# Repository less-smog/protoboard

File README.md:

TODO:

* Align I2C output pins with the rest, so that the pins can be plugged into the edge of a protoboard.
* Move resistors and diodes to reduce offset from the edge - ideally there should be none.
* SDS011 connector should be an angled connector, close to the edge of the board.

## Subtree workflow

### Inject

```
git subtree add --prefix vendor/lolin https://github.com/tommck/LoLin_Designs.git master --squash
```

### Update

```
git subtree pull --prefix vendor/lolin https://github.com/tommck/LoLin_Designs.git master --squash
```

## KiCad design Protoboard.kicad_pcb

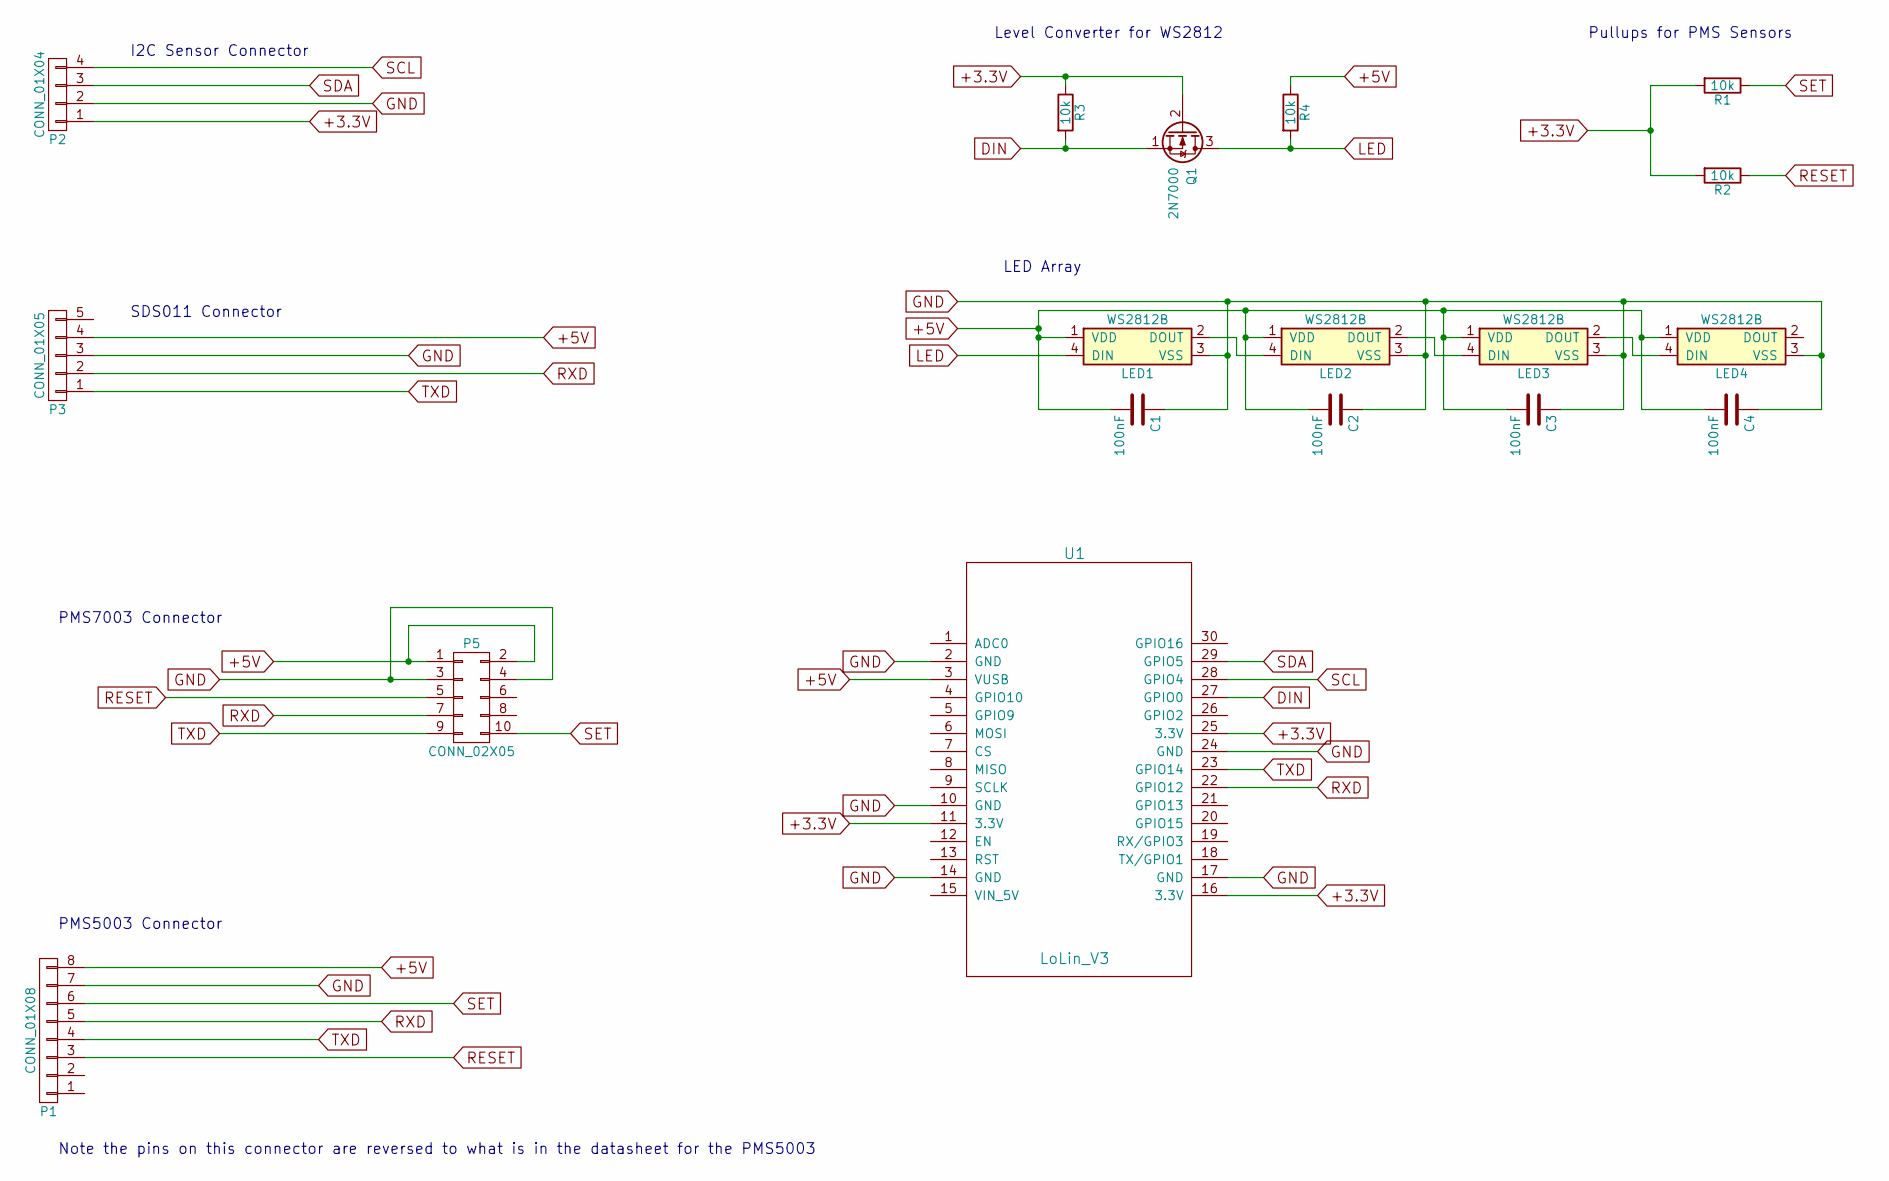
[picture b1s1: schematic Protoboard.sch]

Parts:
C1, C2, C3, C4: 100nF; C_1206_HandSoldering
LED1, LED2, LED3, LED4: WS2812B; LED_WS2812B-PLCC4
P1: CONN_01X08; Molex_PicoBlade_53261-0871_08x1.25mm_Angled
P2: CONN_01X04; Pin_Header_Straight_1x04
P3: CONN_01X05; JST_XH_S05B-XH-A_05x2.50mm_Angled
P5: CONN_02X05; Amphenol
Q1: 2N7000; TO-92_Inline_Wide
R1, R2, R3, R4: 10k; Resistor_Horizontal_RM7mm
U1: LoLin_V3; LoLin

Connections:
+3.3V: P2.1, Q1.2 (G), R1.2, R2.2, R3.1, U1.11 (3.3V), U1.16 (3.3V), U1.25 (3.3V)
+5V: C1.2, C2.2, C3.2, C4.2, LED1.1 (VDD), LED2.1 (VDD), LED3.1 (VDD), LED4.1 (VDD), P1.8, P3.4, P5.1, P5.2, R4.1, U1.3 (VUSB)
DIN: Q1.1 (S), R3.2, U1.27 (GPIO0)
GND: C1.1, C2.1, C3.1, C4.1, LED1.3 (VSS), LED2.3 (VSS), LED3.3 (VSS), LED4.3 (VSS), P1.7, P2.2, P3.3, P5.3, P5.4, U1.2 (GND), U1.10 (GND), U1.14 (GND), U1.17 (GND), U1.24 (GND)
LED: LED1.4 (DIN), Q1.3 (D), R4.2
unnamed: LED1.2 (DOUT), LED2.4 (DIN)
unnamed: LED2.2 (DOUT), LED3.4 (DIN)
unnamed: LED3.2 (DOUT), LED4.4 (DIN)
RESET: P1.3, P5.5, R2.1
RXD: P1.5, P3.2, P5.7, U1.22 (GPIO12)
SCL: P2.4, U1.28 (GPIO4)
SDA: P2.3, U1.29 (GPIO5)
SET: P1.6, P5.10, R1.1
TXD: P1.4, P3.1, P5.9, U1.23 (GPIO14)

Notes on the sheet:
I2C Sensor Connector
SDS011 Connector
PMS7003 Connector
PMS5003 Connector
Pullups for PMS Sensors
Level Converter for WS2812
Note the pins on this connector are reversed to what is in the datasheet for the PMS5003
LED Array

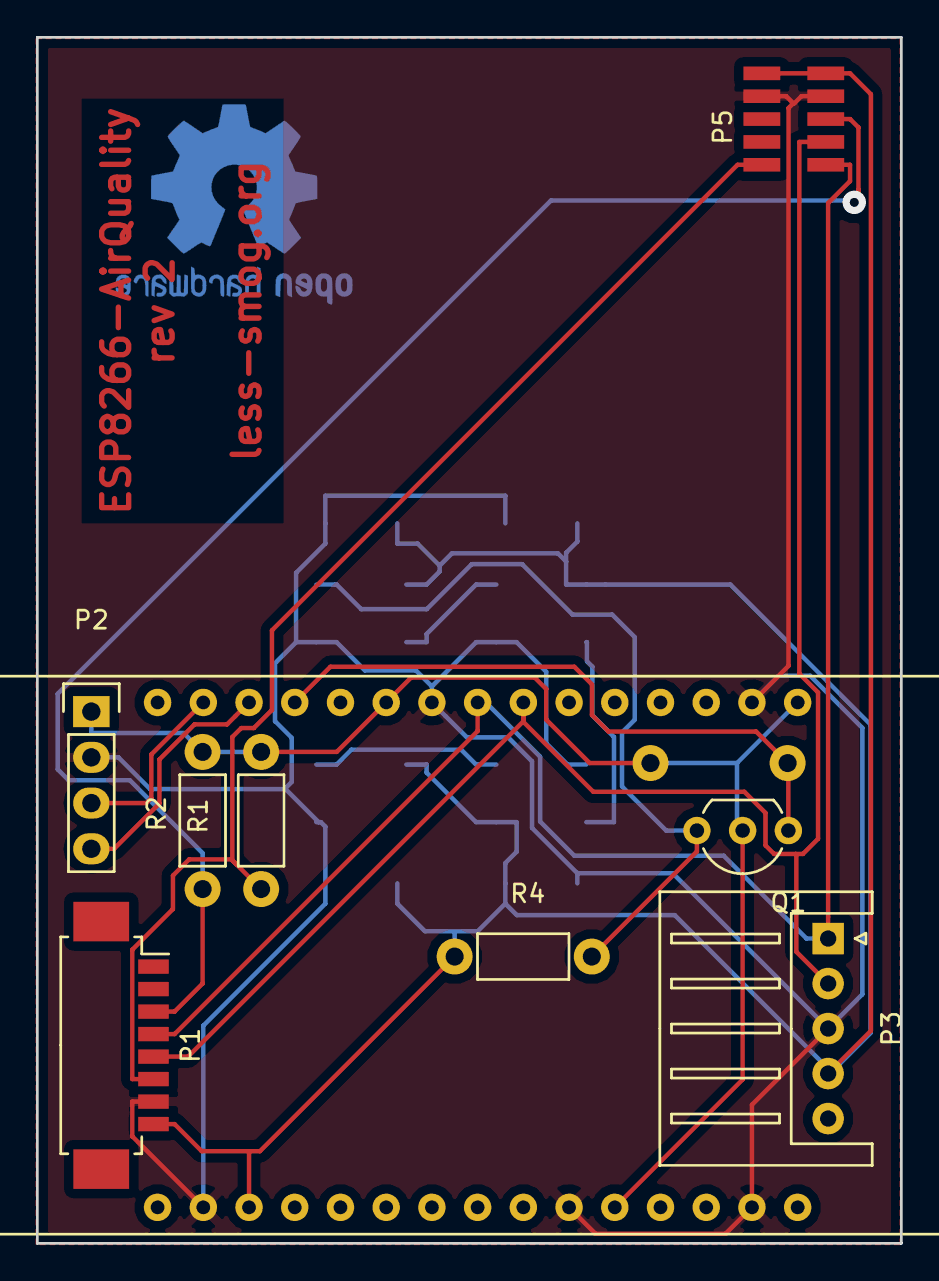
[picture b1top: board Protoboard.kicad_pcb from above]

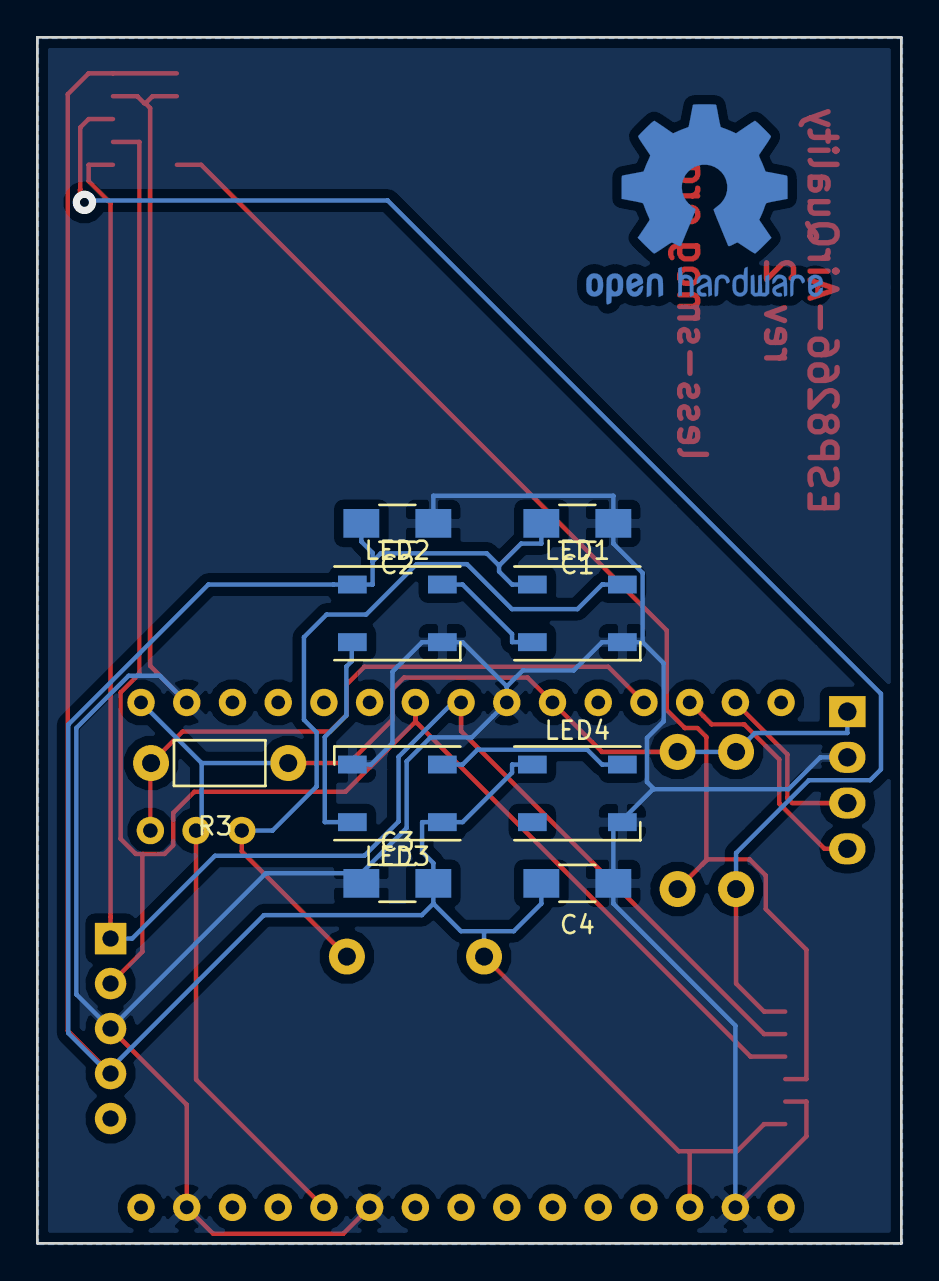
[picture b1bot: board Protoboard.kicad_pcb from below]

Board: 2 copper layers, 48.0 x 67.0 mm, 18 parts (9 on the bottom side), 14 nets.

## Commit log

2017-03-11 Initial commit.
2017-03-11 Updated footprints for most things.
2017-03-12 Added a drawing for RS part no http://uk.rs-online.com/web/p/pcb-sockets/7944590/?sra=pstk
2017-03-12 Routing done.
2017-03-13 Generated drill files and stencils.
2017-03-14 Moved tracks around.
2017-03-14 Added holes to denote corners of the board. Regenerated outputs.
2017-03-15 Added sample image.
2017-03-18 Reorganized board, fixed bug with Molex Microblade connector (reversed pins).
2017-03-19 Improved track spacing for home brew UV etching.
2017-03-20 Non-reversed drill file.
2017-03-20 Added another photo and updated README with TODO items.
2017-03-20 Add .giti to .gitignore
2017-03-31 Added WS2812B leds.
2017-03-31 Minor changes.
2017-03-31 Squashed 'vendor/lolin/' content from commit abab765
    git-subtree-dir: vendor/lolin
    git-subtree-split: abab76525bdcf2ff2177c4e4450d0f7e94bf356f
2017-03-31 Routing and fill zones.
2017-03-31 Fab outputs.
2017-03-31 Moved PMS7003 connector 4mm towards the edge and regenerated all fab artifacts.
2017-03-31 Tigten boards together to fix on a 10x16 cm board.
2017-04-01 Removed drilling holes from corners and regenerated drill file.
2017-04-08 Removed gerber files.
    This is rev 2
2017-04-08 Print options?
2017-05-11 Adjusted via sized for production.
    Inner fi = 0.4mm min
    Outer fi = 1.2mm min
